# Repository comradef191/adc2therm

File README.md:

# ATTENTION: ACTUAL PCBS NOT YET TESTED
**MY PCBS HAVE NOT YET ARRIVIED, THUS I HAVE NOT YET BEEN ABLE TO TEST THIS BOARD AND ITS STABILITY. FEEL FREE TO JOIN MY [DISCORD](https://discord.gg/cMK9gxetGT) FOR UPDATES; THIS NOTICE WILL BE REMOVED ONCE MY BOARDS ARRIVE AND I AM ABLE TO PERFORM SOME TESTING.**
___

# About
This is a simple PCB implementing the support circuitry necessery to properly connect a Thermistor to an ADC pin.

While originally intended to be used with the [SKR Pico](https://bttwiki.com/SKR%20Pico.html)'s `SERVO` port to add a port for a chamber thermistor, this board should have universal compatability.

It should be noted that this board uses 0603 SMD components, and as such hand-assembly may be more tricky to novices, though I have made sure to use the enlarged hand-assembly footprints.

___
# Bill Of Materials
| Component          |No. Needed|Cost (Total)|Comment|Sourcing URL|
|--------------------|----------|------------|-------|-------|
|JST XH 1x2          | 3        | $0.65      |MoQ=100|https://www.lcsc.com/product-detail/Wire-To-Board-Connector_DEALON-XH-D-2A_C5160911.html|
|Ferrite Bead        | 1        | $0.51      |MoQ=50 |https://www.lcsc.com/product-detail/Ferrite-Beads_Murata-Electronics-BLM18KG121TN1D_C85831.html|
|4.7k 0.1% Resistor  | 1        | $0.84      |MoQ=50 |https://www.lcsc.com/product-detail/Chip-Resistor-Surface-Mount_UNI-ROYAL-Uniroyal-Elec-TC0350B4701T5F_C2989672.html|
|100nF 10v Capacitor | 1        | $0.31      |MoQ=100|https://www.lcsc.com/product-detail/Multilayer-Ceramic-Capacitors-MLCC-SMD-SMT_YAGEO-CC0603KRX7R6BB104_C519438.html|
|2.2uF 10v Capacitor | 1        | $0.43      |MoQ=100|https://www.lcsc.com/product-detail/Multilayer-Ceramic-Capacitors-MLCC-SMD-SMT_Samwha-Capacitor-CS1608X5R225K100NRB_C5189830.html|

MoQ cost of $2.74. This is enough for 30 PCBs, making for $0.09 in parts per board, before shipping, tax and PCB costs.

The cost for 75 boards, Including shipping, PCBs, and parts, is aprox $23.31 and £0.31 per board

___
# LICENSE
This source describes Open Hardware and is licensed under the CERN-OHL-S v2 or any later version.
You may redistribute and modify this source and make products using it under the terms of the CERN-OHL-S v2. (https://ohwr.org/cern_ohl_s_v2.txt)

This source is distributed WITHOUT ANY EXPRESS OR IMPLIED WARRANTY, INCLUDING OF MERCHANTABILITY, SATISFACTORY QUALITY AND FITNESS FOR A PARTICULAR PURPOSE. Please see the CERN-OHL-S v2 for applicable conditions.

Source location: https://github.com/comradef191/adc2therm

As per CERN-OHL-S v2 section 4, should You produce hardware based on this source, You must where practicable maintain the Source Location visible on the PCB.

___

*I would like to give thanks to @dead.lock for providing feedback on my analogue layout.*

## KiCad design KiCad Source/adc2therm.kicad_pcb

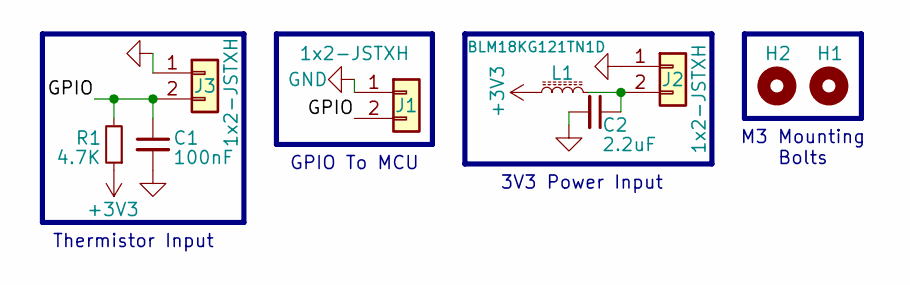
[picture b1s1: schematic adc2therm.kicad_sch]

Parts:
C1: 100nF; C_0603_1608Metric_Pad1.05x0.95mm_HandSolder; LCSC C519438
C2: 2.2uF; C_0603_1608Metric_Pad1.05x0.95mm_HandSolder; LCSC C5189830
H1, H2: MountingHole; MountingHole_3.2mm_M3_ISO7380
J1, J2, J3: 1x2-JSTXH; JST-XH_1x02-V ~ Custom; LCSC C5160911
L1: BLM18KG121TN1D; L_0603_1608Metric_Pad1.05x0.95mm_HandSolder; LCSC C85831
R1: 4.7K; R_0603_1608Metric_Pad0.98x0.95mm_HandSolder; LCSC C2989672

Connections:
+3V3: L1.1, R1.1
/GPIO: C1.1, J1.2, J3.2, R1.2
GND: C1.2, C2.2, J1.1, J2.1, J3.1
unnamed: C2.1, J2.2, L1.2

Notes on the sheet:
GPIO To MCU
M3 Mounting Bolts
3V3 Power Input
Thermistor Input

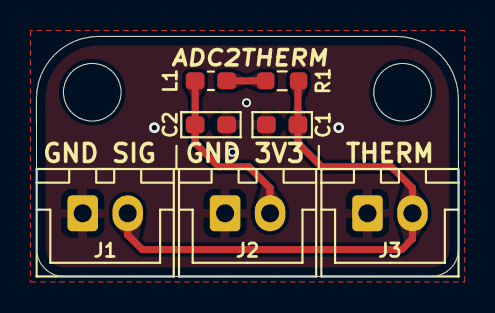
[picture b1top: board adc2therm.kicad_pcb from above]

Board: 2 copper layers, 23.4 x 13.3 mm, 9 parts (0 on the bottom side), 4 nets.

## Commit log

2024-06-04 Add KiCad source files
2024-06-04 woops
2024-06-04 Add non-EDA source files, add size info to PCB
2024-06-04 Final PCB cleanup
2024-06-04 Add license and detail-out the ReadMe

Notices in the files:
KiCad Source/adc2therm.kicad_pcb:
CERN OHL v2 -S
